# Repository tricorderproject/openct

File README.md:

openct
======

Open Source Computed Tomography (CT) Scanner <br>
http://www.tricorderproject.org/openct <br>
Copyright (C) 2014  Peter Jansen and the Tricorder project <br>
peter@tricorderproject.org <br>

*Early alpha release v0.1*

# Introduction

The Open Source Computed Tomography (CT) Scanner project aims to move towards creating an inexpensive and open desktop computed tomography scanner for academic and educational purposes.  The most common form of computed tomography is radiographic using x-rays or gamma rays, although it is my hope that this project can serve as a general platform for other kinds of tomographic research with other, safer wavelengths. 

This project is intended for use with radioisotope "check" sources that are many orders of magnitude less intense than sources in a commercial or medical radiographic setups.  This means that even very low resolution images will take hours of measurement and integration time to assemble, and the resolution and signal to noise ratio of a scan are largely a function of time (and patience).  Much of the spirit of this project is to move towards creating better scans through the use of clever signal processing techniques or wavelengths that can be more efficiently detected, rather than increasing source intensity. 

# Open Source

This project is open hardware and is released under various open licenses.  Please see LICENSES.TXT for details.

For potential contributors, a list of suggested contributions and next steps can be found in TODO.TXT .

# Warning

This project has a variety of dangers associated with it, including (without limitation) its assembly and use.  This generally includes the typical hazards involved with assembling, testing, and using electronics projects, CNC projects, as well as using hand tools, power tools, and CNC manufacturing tools such as laser cutters or CNC routers.  This is not a first project in any of these areas, and one should be well experienced and comfortable in all aspects of this project's design, assembly, and use. 

In addition, for radiography this project makes use of a low intensity sealed radioactive radioisotope source.  You should be experienced and extremely comfortable with handling and using radioactive sources, understanding the potential dangers (and how to minimize them), as well as any local laws or regulations regarding such material.  Having advanced training in medical imaging, radiography, and/or radiation biophysics is highly recommended.  

In no case should any living thing be placed inside of or be scanned by the device. 

**DISCLAIMER OF WARRANTIES AND LIMITATION OF LIABILITY.**

UNLESS OTHERWISE SEPARATELY UNDERTAKEN BY THE LICENSOR, TO THE EXTENT POSSIBLE, THE LICENSOR OFFERS THE LICENSED MATERIAL AS-IS AND AS-AVAILABLE, AND MAKES NO REPRESENTATIONS OR WARRANTIES OF ANY KIND CONCERNING THE LICENSED MATERIAL, WHETHER EXPRESS, IMPLIED, STATUTORY, OR OTHER. THIS INCLUDES, WITHOUT LIMITATION, WARRANTIES OF TITLE, MERCHANTABILITY, FITNESS FOR A PARTICULAR PURPOSE, NON-INFRINGEMENT, ABSENCE OF LATENT OR OTHER DEFECTS, ACCURACY, OR THE PRESENCE OR ABSENCE OF ERRORS, WHETHER OR NOT KNOWN OR DISCOVERABLE. WHERE DISCLAIMERS OF WARRANTIES ARE NOT ALLOWED IN FULL OR IN PART, THIS DISCLAIMER MAY NOT APPLY TO YOU.

TO THE EXTENT POSSIBLE, IN NO EVENT WILL THE LICENSOR BE LIABLE TO YOU ON ANY LEGAL THEORY (INCLUDING, WITHOUT LIMITATION, NEGLIGENCE) OR OTHERWISE FOR ANY DIRECT, SPECIAL, INDIRECT, INCIDENTAL, CONSEQUENTIAL, PUNITIVE, EXEMPLARY, OR OTHER LOSSES, COSTS, EXPENSES, OR DAMAGES ARISING OUT OF THIS PUBLIC LICENSE OR USE OF THE LICENSED MATERIAL, EVEN IF THE LICENSOR HAS BEEN ADVISED OF THE POSSIBILITY OF SUCH LOSSES, COSTS, EXPENSES, OR DAMAGES. WHERE A LIMITATION OF LIABILITY IS NOT ALLOWED IN FULL OR IN PART, THIS LIMITATION MAY NOT APPLY TO YOU.

THE DISCLAIMER OF WARRANTIES AND LIMITATION OF LIABILITY PROVIDED ABOVE SHALL BE INTERPRETED IN A MANNER THAT, TO THE EXTENT POSSIBLE, MOST CLOSELY APPROXIMATES AN ABSOLUTE DISCLAIMER AND WAIVER OF ALL LIABILITY.

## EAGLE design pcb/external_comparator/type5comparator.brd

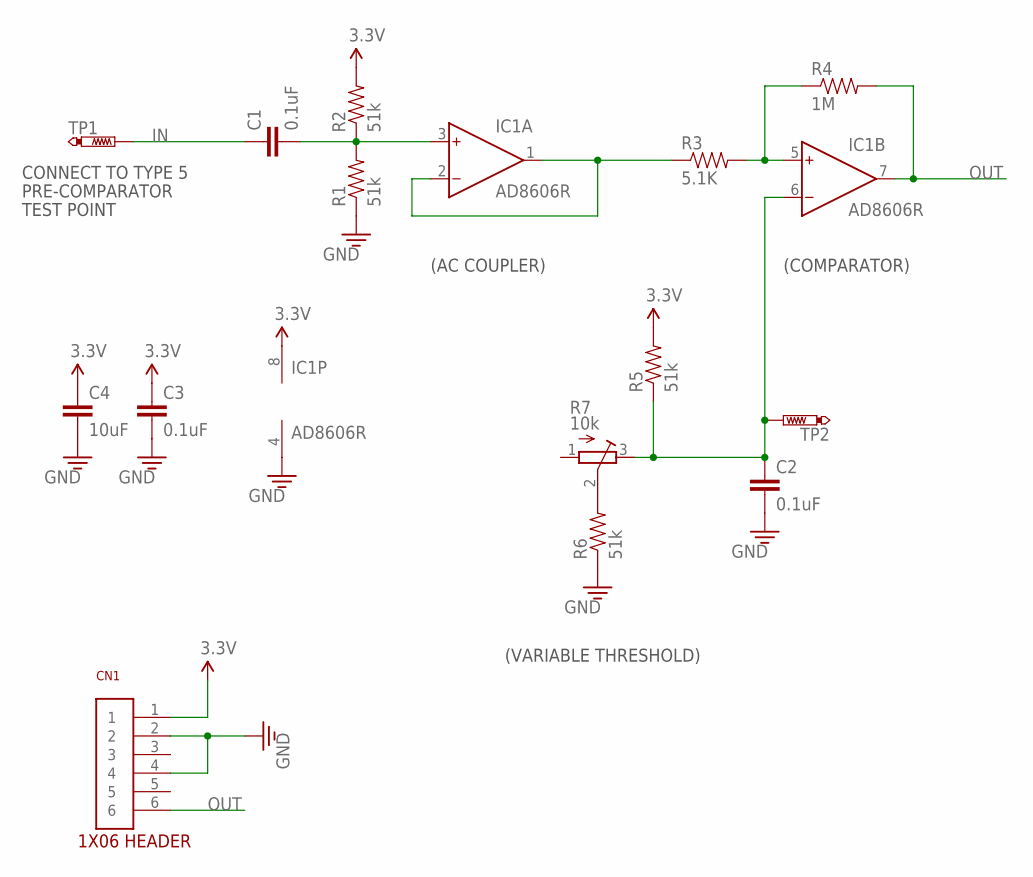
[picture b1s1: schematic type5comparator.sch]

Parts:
C1, C2, C3: 0.1uF; 0603
C4: 10uF; 0603
CN1: 1X06
IC1: AD8606R; SO8
R1, R2, R5, R6: 51k; 0603
R3: 5.1K; 0603
R4: 1M; 0603
R7: 10k; RTRIM3299W
TP1, TP2: PTR1PAD1-13; P1-13

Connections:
3.3V: C3.1, C4.1, CN1.1, IC1.8 (V+), R2.2, R5.2
GND: C2.2, C3.2, C4.2, CN1.2, CN1.4, IC1.4 (V-), R1.1, R6.1
IN: C1.1, TP1.TP
unnamed: R6.2, R7.2 (S)
unnamed: C1.2, IC1.3 (IN+), R1.2, R2.1
unnamed: IC1.1 (OUT), IC1.2 (IN-), R3.1
unnamed: IC1.5 (IN+), R3.2, R4.1
unnamed: C2.1, IC1.6 (IN-), R5.1, R7.3 (A), TP2.TP
OUT: CN1.6, IC1.7 (OUT), R4.2

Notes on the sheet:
(AC COUPLER)
(COMPARATOR)
(VARIABLE THRESHOLD)
CONNECT TO TYPE 5
PRE-COMPARATOR
TEST POINT

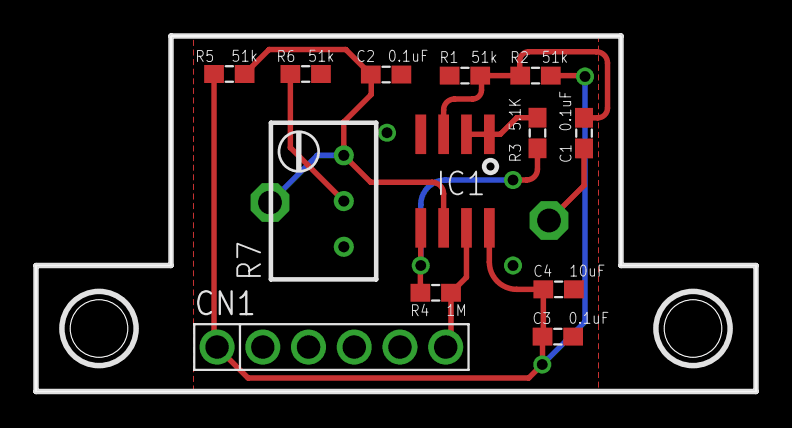
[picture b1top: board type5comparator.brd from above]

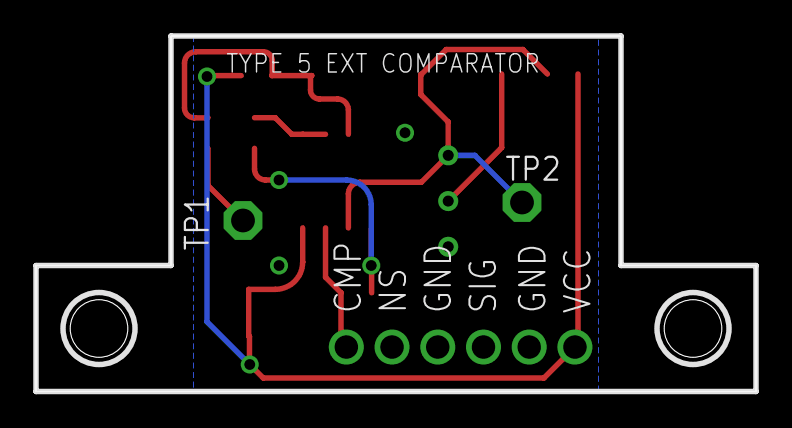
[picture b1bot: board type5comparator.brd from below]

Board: 2 copper layers, 40.0 x 19.8 mm, 15 parts (2 on the bottom side), 9 nets.

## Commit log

2014-03-22 Initial alpha release v0.1
2014-08-07 Added PDF of Type 5 external comparator schematic
